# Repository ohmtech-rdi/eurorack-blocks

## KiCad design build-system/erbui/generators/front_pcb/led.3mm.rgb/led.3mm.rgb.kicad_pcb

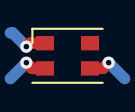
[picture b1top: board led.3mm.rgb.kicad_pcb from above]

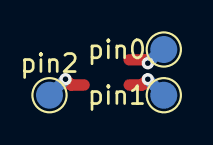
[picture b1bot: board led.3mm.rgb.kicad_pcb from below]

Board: 2 copper layers, 4 parts (3 on the bottom side), 3 nets.

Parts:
Pin0, Pin1, Pin2: TestPoint; TestPoint_Pad_D1.5mm
ZZ1: LED_RGBA; LED_Cree-PLCC4_3.2x2.8mm_CCW

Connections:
unnamed: Pin0.1, ZZ1.1
unnamed: Pin1.1, ZZ1.2
unnamed: Pin2.1, ZZ1.3
